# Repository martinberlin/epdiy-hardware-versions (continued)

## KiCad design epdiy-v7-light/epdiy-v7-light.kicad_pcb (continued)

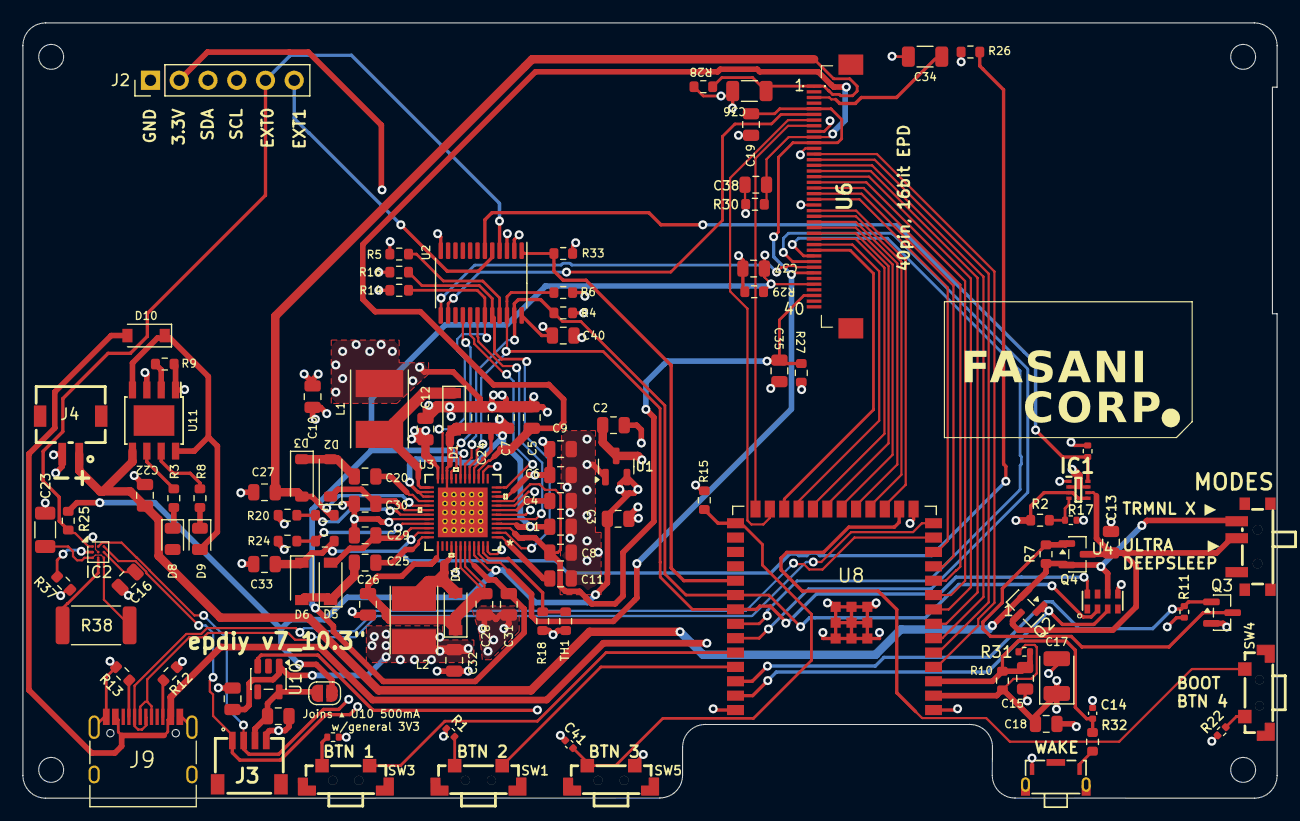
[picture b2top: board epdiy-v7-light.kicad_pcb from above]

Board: 4 copper layers, 110.8 x 68.5 mm, 117 parts (0 on the bottom side), 90 nets.

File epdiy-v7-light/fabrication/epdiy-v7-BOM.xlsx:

epdiy-v7-BOM
Comment | Designator | Footprint | LCSC
4.7uF | C1,C4,C5,C7,C8,C11,C24,C26,C28,C31 | Capacitor_SMD:C_0805_2012Metric | C1779
1uF | C14 | Capacitor_SMD:C_0402_1005Metric | C162161
100nF | C15,C22,C29,C30,C40 | Capacitor_SMD:C_0805_2012Metric | C49678
2.2uF | C16,C27,C33 | Capacitor_SMD:C_0805_2012Metric | C49217
100uF | C17 | Capacitor_Tantalum_SMD:CP_EIA-3528-15_AVX-H | C16133
1uF | C18 | Capacitor_SMD:C_0805_2012Metric | C28323
10uF | C2,C3,C9,C12,C13,C19,C21,C32,C39 | Capacitor_SMD:C_0805_2012Metric | C15850
10nF | C20,C25 | Capacitor_SMD:C_0805_2012Metric | C1710
1uF/50V | C23,C34,C36 | Capacitor_SMD:C_1206_3216Metric | C1848
1uF/25V | C35,C37,C38 | Capacitor_SMD:C_0805_2012Metric | C28323
22pF | C41 | Capacitor_SMD:C_0402_1005Metric | C5119318
22uF | C6,C10 | Capacitor_SMD:C_0805_2012Metric | C45783
MBR0540 | D1,D2,D3,D4,D5,D6 | Diode_SMD:D_SOD-123 | C21353
1N5817 | D10 | Diode_SMD:D_SOD-123 | C8598
LED GREEN | D8 | LED_SMD:LED_0805_2012Metric | C2297
LED RED | D9 | LED_SMD:LED_0805_2012Metric | C84256
TPS2117DRLR | IC1 | footprints:C22399676_TPS2117-8N | C3235557
BQ27426YZFR | IC2 | Package_BGA:Texas_DSBGA-9_1.62x1.58mm_Layout3x3_P0.5mm | C165137
SM04B-SRSS-TB_LF__SN_ | J3 | footprints:QWIIC_SM04B-SRSS-TB_LFSN_ | C160404
Conn_01x02_Shielded | J4 | footprints:C265329_BATT_S2B-ZR-SM4A | C265329
USB_C_Receptacle_USB2.0 | J9 | Connector_USB:USB_C_Receptacle_HRO_TYPE-C-31-M-12 | C165948
4.7uH | L1 | Inductor_SMD:L_Taiyo-Yuden_NR-50xx_HandSoldering | C222947
2.2uH | L2 | Inductor_SMD:L_Taiyo-Yuden_NR-40xx_HandSoldering | C92959
CPH3350 | Q2,Q4 | Package_TO_SOT_SMD:SOT-23 | C7494437
NTR4170NT1G | Q3 | Package_TO_SOT_SMD:SOT-23 | C236116
10k | R1,R21,R22,R31 | Resistor_SMD:R_0402_1005Metric | C4322213
10k | R10,R14,R15,R16,R25,R33,R37 | Resistor_SMD:R_0603_1608Metric | C25804
100k | R11,R35 | Resistor_SMD:R_0402_1005Metric | C102750
2k | R17 | Resistor_SMD:R_0402_1005Metric | C4109
43k | R18 | Resistor_SMD:R_0603_1608Metric | C23172
1M | R19,R23 | Resistor_SMD:R_0603_1608Metric | C22935
5.1k | R2,R4,R6,R12,R13 | Resistor_SMD:R_0603_1608Metric | C23186
52.3k | R20 | Resistor_SMD:R_0603_1608Metric | C23196
47.5k | R24 | Resistor_SMD:R_0603_1608Metric | C25819
47k | R26,R27,R28,R29 | Resistor_SMD:R_0603_1608Metric | C25819
1k | R3,R8 | Resistor_SMD:R_0603_1608Metric | C21190
0Ω | R32 | Resistor_SMD:R_0603_1608Metric | C21189
10m | R38 | Resistor_SMD:R_2512_6332Metric | C323803
0 | R5 | Resistor_SMD:R_0603_1608Metric | C21189
100k | R7,R30 | Resistor_SMD:R_0603_1608Metric | C25803
3.83k | R9 | Resistor_SMD:R_0603_1608Metric | C103591
HX-3X6X3.5-CA-0.6-2.5N | SW1,SW3,SW4,SW5 | footprints:SW-SMD_HX-3X6X3.5-CA-0.6-2.5N | C49234146
HX TS24CB 160GF | SW2 | footprints:C25168832_TS24CB-160GF | C25168832
MK-12C02-G015 | SW6 | footprints:C2911519_switch-MK-12C02-G020 | C963206
10k/3380K | TH1 | Resistor_SMD:R_0603_1608Metric | C76589
MCP1700-3302E_SOT23 | U1 | Package_TO_SOT_SMD:SOT-23 | C39051
RT9080-33GJ5 | U10 | Package_TO_SOT_SMD:TSOT-23-5 | C841192
TP4056 | U11 | epaper-breakout:TP4056_SOP-8-PP | C16581
PCA9535PW | U2 | Package_SO:TSSOP-24_4.4x7.8mm_P0.65mm | C255606
TPS651851RSLR | U3 | epaper-breakout:TPS651851RSLR | C139292
DS3231MZ | U4 | Package_SO:SOIC-8_3.9x4.9mm_P1.27mm | C107410
ED078KH6 | U6 | footprints:FH1240S05SH55_MIRRORED | C202114

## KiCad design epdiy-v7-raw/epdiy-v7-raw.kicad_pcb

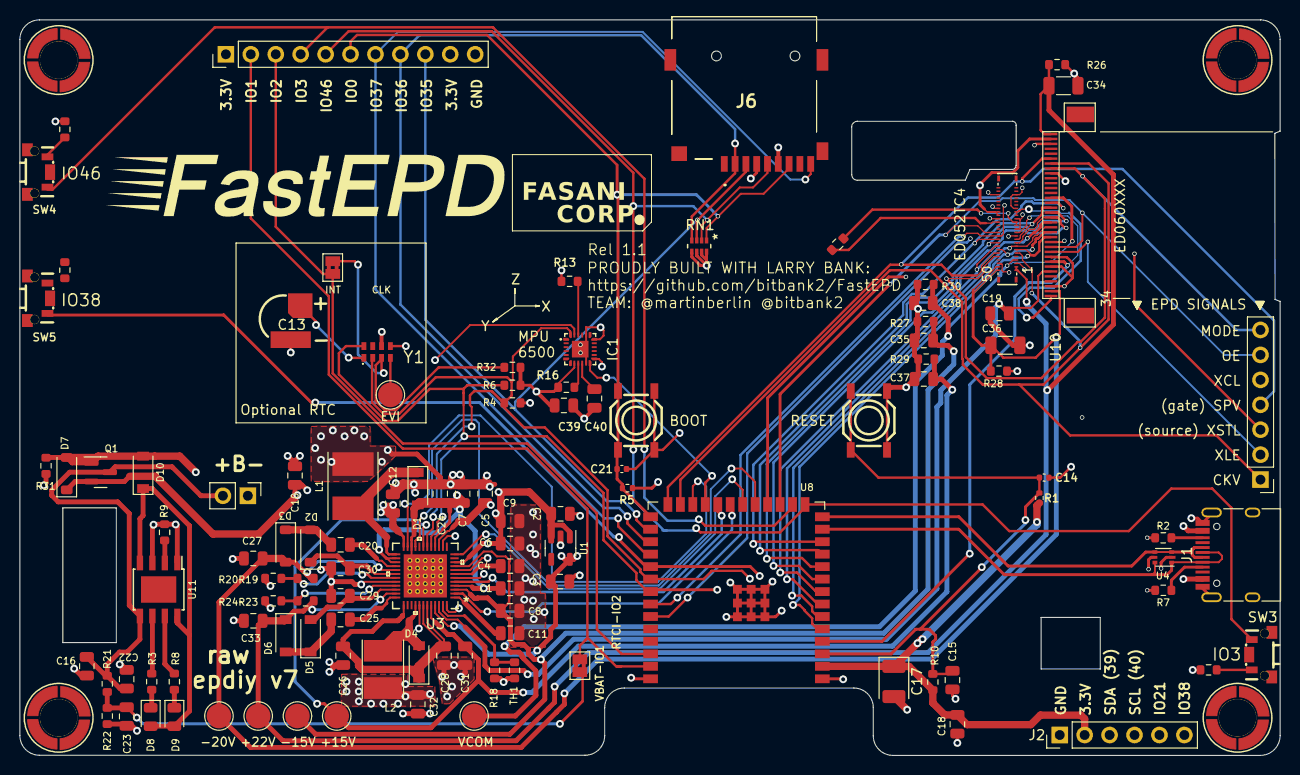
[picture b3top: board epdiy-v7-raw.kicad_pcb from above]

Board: 4 copper layers, 128.4 x 74.9 mm, 117 parts (0 on the bottom side), 80 nets.

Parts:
C1, C4, C5, C7, C8, C11, C24, C26, C28, C31: 4.7uF; C_0805_2012Metric
C2, C3, C9, C12, C16, C19, C32: 10uF; C_0805_2012Metric
C6, C10: 22uF; C_0805_2012Metric
C13: superCAP; C9900013866_SUPERCAP-TH_XH414HG
C14: 1uF; C_0402_1005Metric
C15, C22, C23, C29, C30, C40: 100nF; C_0805_2012Metric
C17: 100uF; CP_EIA-3528-15_AVX-H
C18, C39: 1uF; C_0805_2012Metric
C20, C25: 10nF; C_0805_2012Metric
C21: 22pF; C_0402_1005Metric
C27, C33: 2.2uF; C_0805_2012Metric
C34, C36: 1uF/50V; C_1206_3216Metric
C35, C37, C38: 1uF/25V; C_0805_2012Metric
CN1: WP27D-S050VA3-R15000; CONN-SMD_50P-P0.35_WP27D-S050VA3
D1, D2, D3, D4, D5, D6, D7: MBR0540; D_SOD-123
D8: LED GREEN; LED_0805_2012Metric
D9: LED RED; LED_0805_2012Metric
D10: 1N5817; D_SOD-123
H1, H2, H3, H4: MountingHole; C2916320_SMTSO2015CTJ
IC1: MPU-6500; C50278_IMU_QFN-24_L3.0-W3.0-P0.40-BL-EP
J1: USB_C_Receptacle_USB2.0; USB_C_Receptacle_HRO_TYPE-C-31-M-12
J2: EXTENSION_HEADER; PinHeader_1x06_P2.54mm_Vertical
J3: SIGNALS_HEADER; PinHeader_1x07_P2.54mm_Vertical
J5: CONN_BAT; PinHeader_1x02_P2.54mm_Vertical
J6: THD2528-11SD-GF; MicroSD_THD252811SDGF
J7: ESP_HDR; PinHeader_1x11_P2.54mm_Vertical
JP1: VBAT_GPIO1; SolderJumper-2_P1.3mm_Bridged2Bar_Pad1.0x1.5mm
JP2: RTCINT_GPIO2; SolderJumper-2_P1.3mm_Bridged2Bar_Pad1.0x1.5mm
L1: 4.7uH; L_Taiyo-Yuden_NR-50xx_HandSoldering
L2: 2.2uH; L_Taiyo-Yuden_NR-40xx_HandSoldering
Q1: AO3401A; SOT-23
R1, R5: 10k; R_0402_1005Metric
R2, R4, R6, R7: 5.1k; R_0603_1608Metric
R3, R8: 2.4k; R_0603_1608Metric
R9: 3.83k; R_0603_1608Metric
R10, R13, R16, R32: 10k; R_0603_1608Metric
R11, R12, R14, R15: 10K; R_0603_1608Metric
R18: 43k; R_0603_1608Metric
R19, R23: 1M; R_0603_1608Metric
R20: 52.3k; R_0603_1608Metric
R21: 680k; R_0603_1608Metric
R22: 150k; R_0603_1608Metric
R24: 47.5k; R_0603_1608Metric
R26, R27, R28, R29: 47k; R_0603_1608Metric
R30, R31: 100k; R_0603_1608Metric
RN1: R_Pack04; RESN_F392JTCE_UNR_SD-pullup
SW1, SW2: TC-0522C-1.7-160G; C2845289_SW-SMD_4P-L5.2-W5.2-P3.70-LS6.4
SW3, SW4, SW5: K2-1806SQ-A2DW-04; C5143621_KEY-SMD_TS24ZJ
TH1: 10k/3380K; R_0603_1608Metric
TP1: +22V; TestPoint_Pad_D2.5mm
TP2: -15V; TestPoint_Pad_D2.5mm
TP3: -20V; TestPoint_Pad_D2.5mm
TP4: +15V; TestPoint_Pad_D2.5mm
TP5: VCOM; TestPoint_Pad_D2.5mm
TP6: EVI; TestPoint_Pad_D2.5mm
U1: RT9080-33GJ5; TSOT-23-5
U3: TPS651851RSLR
U4: USBLC6-2P6; SOT-666
U8: ESP32-S3-WROOM-1
U10: ED060XC5; X05A20H34G
U11: TP4056; TP4056_SOP-8-PP
Y1: RV-3032-C7; RV3032C7

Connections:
3.3V: C3.2, C17.1, C18.2, C39.2, IC1.8 (VDDIO), IC1.13 (VDD), J2.2, J6.4 (VDD), J7.1, J7.10, R1.2, R4.1, R5.2, R6.1, R10.2, R13.2, R16.2, R32.2, RN1.5 (R4.2), RN1.6 (R3.2), RN1.7 (R2.2), RN1.8 (R1.2), U1.5 (VOUT), U3.45 (VIN3P3), U8.2 (3V3), Y1.6 (VDD)
/15V: C31.2, C37.1, CN1.33, CN1.34, R29.1, TP4.1, U3.19 (VPOS_DIS), U3.44 (VPOS), U10.33 (VPOS)
/+22V: C33.1, C34.1, CN1.1, CN1.2, D6.1 (K), R23.1, R26.1, TP1.1, U3.35 (VDDH_DIS), U10.34 (VGG)
/-15V: C8.2, C35.1, CN1.17, CN1.18, R27.1, TP2.1, U3.3 (VNEG), U3.9 (VNEG_DIS), U10.1 (VNEG)
/-20V: C27.2, C36.1, CN1.49, CN1.50, D3.2 (A), R19.1, R28.1, TP3.1, U3.29 (VEE_DIS), U10.2 (VEE)
/ADD_69: IC1.9 (SDO_/_AD0), R16.1
/CKV: CN1.6, J3.1, U8.25 (GPIO48/SPICLK_N/SUBSPICLK_N_DIFF), U10.28 (CKV)
/D0: CN1.7, U8.5 (GPIO5/TOUCH5/ADC1_CH4), U10.13 (D0)
/D1: CN1.44, U8.6 (GPIO6/TOUCH6/ADC1_CH5), U10.14 (D1)
/D2: CN1.8, U8.7 (GPIO7/TOUCH7/ADC1_CH6), U10.15 (D2)
/D3: CN1.43, U8.8 (GPIO15/U0RTS/ADC2_CH4/XTAL_32K_P), U10.16 (D3)
/D4: CN1.9, U8.9 (GPIO16/U0CTS/ADC2_CH5/XTAL_32K_NH5), U10.17 (D4)
/D5: CN1.42, U8.10 (GPIO17/U1TXD/ADC2_CH6), U10.18 (D5)
/D6: CN1.10, U8.11 (GPIO18/U1RXD/ADC2_CH7/CLK_OUT3), U10.19 (D6)
/D7: CN1.41, U8.12 (GPIO8/TOUCH8/ADC1_CH7/SUBSPICS1), U10.20 (D7)
/EN: C14.2, C15.1, R1.1, R10.1, SW1.3, SW1.4, U8.3 (EN)
/EP_MODE: CN1.46, J3.7, U8.18 (GPIO10/TOUCH10/ADC1_CH9/FSPICS0/FSPIIO4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), U10.27 (MODE1)
/EP_OE: CN1.39, J3.6, U8.17 (GPIO9/TOUCH9/ADC1_CH8/FSPIHD/SUBSPIHD), U10.11 (XOE)
/EP_SPV: CN1.45, J3.4, U8.26 (GPIO45), U10.29 (SPV)
/EP_VCOM: C5.2, C38.1, CN1.4, R30.1, TP5.1, U3.15 (VCOM), U10.21 (VCOM)
/ESP_USB+: J1.A6 (D+), J1.B6 (D+), U4.3 (I/O2), U4.4 (I/O2), U8.14 (GPIO20/U1CTS/ADC2_CH9/CLK_OUT1/USB_D+)
/ESP_USB-: J1.A7 (D-), J1.B7 (D-), U4.1 (I/O1), U4.6 (I/O1), U8.13 (GPIO19/U1RTS/ADC2_CH8/CLK_OUT2/USB_D-)
/GPIO_1: J7.2, JP1.1 (A), U8.39 (GPIO1/TOUCH1/ADC1_CH0)
/GPIO_2: J7.3, JP2.2 (B), U8.38 (GPIO2/TOUCH2/ADC1_CH1)
/GPIO_3: J6.5 (CLX), J7.5, RN1.2 (R2.1), SW3.2, U8.15 (GPIO3/TOUCH3/ADC1_CH2)
/GPIO_35: J6.3 (CMD), J7.9, RN1.3 (R3.1), U8.28 (SPIIO6/GPIO35/FSPID/SUBSPID)
/GPIO_36: J6.2 (CD/DAT3), J7.8, RN1.4 (R4.1), U8.29 (SPIIO7/GPIO36/FSPICLK/SUBSPICLK)
/GPIO_37: J6.9 (CD), J7.7, U8.30 (SPIDQS/GPIO37/FSPIQ/SUBSPIQ)
/GPIO_38: J2.5, SW5.2, U8.31 (GPIO38/FSPIWP/SUBSPIWP)
/GPIO_46: J7.4, SW4.2, U8.16 (GPIO46)
/IO0: C21.1, J6.7 (DAT0), J7.6, R5.1, RN1.1 (R1.1), SW2.3, SW2.4, U8.27 (GPIO0/BOOT)
/RTC_INT: JP2.1 (A), R32.1, Y1.3 (~INT)
/SCL: IC1.23 (SCL_/_SCLK), J2.4, R6.2, U3.17 (SCL), U8.33 (MTDO/GPIO40/CLK_OUT2), Y1.8 (SCL)
/SDA: IC1.24 (SDA_/_SDI), J2.3, R4.2, U3.18 (SDA), U8.32 (MTCK/GPIO39/CLK_OUT3/SUBSPICS1), Y1.2 (SDA)
/TPS_PWRUP: U3.21 (PWRUP), U8.19 (GPIO11/TOUCH11/ADC2_CH0/FSPID/FSPIIO5/S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)
/TPS_PWR_GOOD: U3.23 (PWR_GOOD), U8.24 (GPIO47/SPICLK_P/SUBSPICLK_P_DIFF)
/TPS_VCOM_CTRL: U3.12 (VCOM_CTRL), U8.20 (GPIO12/TOUCH12/ADC2_CH1/FSPICLK/FSPIIO6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)
/TPS_WAKEUP: U3.5 (WAKEUP), U8.22 (GPIO14/TOUCH14/ADC2_CH3/FSPIWP/FSPIDQS/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)
/TPS_nINT: U3.2 (NINT), U8.21 (GPIO13/TOUCH13/ADC2_CH2/FSPIQ/FSPIIO7/S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)
/VNEG_IN: C1.1, C7.1, C24.1, D1.2 (A), U3.4 (VNEG_IN), U3.16 (VCOM_PWR), U3.22 (PBKG), U3.26 (VN), U3.27 (VEE_IN), U3.49 (EPAD)
/XCL: CN1.12, J3.5, U8.4 (GPIO4/TOUCH4/ADC1_CH3), U10.8 (XCL)
/XLE: CN1.11, J3.2, U8.35 (MTMS/GPIO42), U10.10 (XLE)
/XSTL: CN1.40, J3.3, U8.34 (MTDI/GPIO41/CLK_OUT1), U10.12 (XSTL)
BAT+: C16.2, C22.2, J5.2, Q1.3 (D), R21.1, U11.5 (BAT)
EPD_VDD: C19.1, CN1.14, CN1.15, R11.2, U3.46 (V3P3), U10.6 (VDD)
GND: C1.2, C2.2, C3.1, C4.1, C5.1, C6.1, C7.2, C8.1, C9.2, C10.1, C11.1, C12.2, C13.2, C14.1, C15.2, C16.1, C17.2, C18.1, C19.2, C21.2, C22.1, C23.1, C24.2, C26.1, C27.1, C28.1, C29.1, C30.2, C31.1, C32.1, C33.2, C34.2, C35.2, C36.2, C37.2, C38.2, C39.1, C40.2, CN1.3, CN1.13, CN1.16, CN1.19, CN1.23, CN1.28, CN1.32, CN1.35, CN1.48, IC1.11 (FSYNC), IC1.18 (GND_1), IC1.20 (RESV_2), IC1.25 (GND_2), J1.A1 (GND), J1.A12 (GND), J1.B1 (GND), J1.B12 (GND), J1.S1 (SHIELD), J2.1, J5.1, J6.6 (VSS), J7.11, L1.2, R2.2, R7.2, R9.1, R12.2, R14.2, R15.2, R18.1, R20.2, R22.2, R24.2, R26.2, R27.2, R28.2, R29.2, R30.2, R31.2, SW1.1, SW1.2, SW2.1, SW2.2, TH1.2, U1.2 (GND), U3.6 (DGND), U3.8 (AGND1), U3.14 (VCOM_DIS), U3.32 (PGND2), U3.41 (PGND1), U3.48 (AGND2), U4.2 (GND), U8.1 (GND), U8.40 (GND), U8.41 (GND), U10.3 (VSS), U10.7 (VSS), U10.9 (VSS), U10.26 (VSS), U10.32 (VSS), U11.1 (TEMP), U11.3 (GND), Y1.5 (VSS)
IMU_INT: IC1.12 (INT), J2.6, U8.23 (GPIO21)
unnamed: CN1.36, R11.1
unnamed: D1.1 (K), L1.1, U3.25 (VN_SW)
unnamed: C20.1, D2.2 (A), D3.1 (K)
unnamed: C30.1, D2.1 (K), U3.30 (VEE_D)
unnamed: D4.2 (A), L2.2, U3.40 (VB_SW)
unnamed: C26.2, C28.2, D4.1 (K), U3.37 (VDDH_IN), U3.42 (VB), U3.43 (VPOS_IN)
unnamed: C29.2, D5.2 (A), U3.34 (VDDH_D)
unnamed: C25.1, D5.1 (K), D6.2 (A)
unnamed: D8.1 (K), R3.2
unnamed: D9.1 (K), R8.2
unnamed: D8.2 (A), D9.2 (A), D10.1 (K), U11.4 (VCC), U11.8 (CE)
unnamed: IC1.22 (NCS), R13.1
unnamed: C40.1, IC1.10 (REGOUT)
unnamed: J1.A5 (CC1), R7.1
unnamed: J1.B5 (CC2), R2.1
unnamed: C23.2, JP1.2 (B), R21.2, R22.1
unnamed: R12.1, SW3.1
unnamed: R14.1, SW4.1
unnamed: R15.1, SW5.1
unnamed: C4.2, U3.7 (INT_LDO)
unnamed: R18.2, TH1.1, U3.47 (TS)
unnamed: C25.2, U3.36 (VDDH_DRV)
unnamed: R23.2, R24.1, U3.33 (VDDH_FB)
unnamed: C20.2, U3.28 (VEE_DRV)
unnamed: R19.2, R20.1, U3.31 (VEE_FB)
unnamed: C11.2, U3.1 (VREF)
unnamed: R9.2, U11.2 (PROG)
unnamed: R8.1, U11.7 (~CHRG)
unnamed: R3.1, U11.6 (~STDBY)
unnamed: TP6.1, Y1.4 (EVI)
VBUS: D7.2 (A), D10.2 (A), J1.A4 (VBUS), J1.A9 (VBUS), J1.B4 (VBUS), J1.B9 (VBUS), Q1.1 (G), R31.1, U4.5 (VBUS)
VDD_RTC: C13.1, Y1.1 (VBACKUP)
VIN: C2.1, C6.2, C9.1, C10.2, C12.1, C32.2, D7.1 (K), L2.1, Q1.2 (S), U1.1 (VIN), U1.3 (EN), U3.10 (VIN), U3.24 (VIN_P)

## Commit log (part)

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2025-05-24 Pending to remove UART + IO expander
2025-09-01 Add kindle 34 pins versions (RAW)
2026-03-19 Update RTC
2026-05-16 Add related repositories to README
    Added related repositories section with links.
